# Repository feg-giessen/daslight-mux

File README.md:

# Daslight MUX #

Encoder to connect multiple buttons to the "port" connection of Daslight DMX interfaces: [http://www.daslight.com/online_manuals/en/750-823-FT8p45-Fj5plXXh3dfPJk8.htm](http://www.daslight.com/online_manuals/en/750-823-FT8p45-Fj5plXXh3dfPJk8.htm)

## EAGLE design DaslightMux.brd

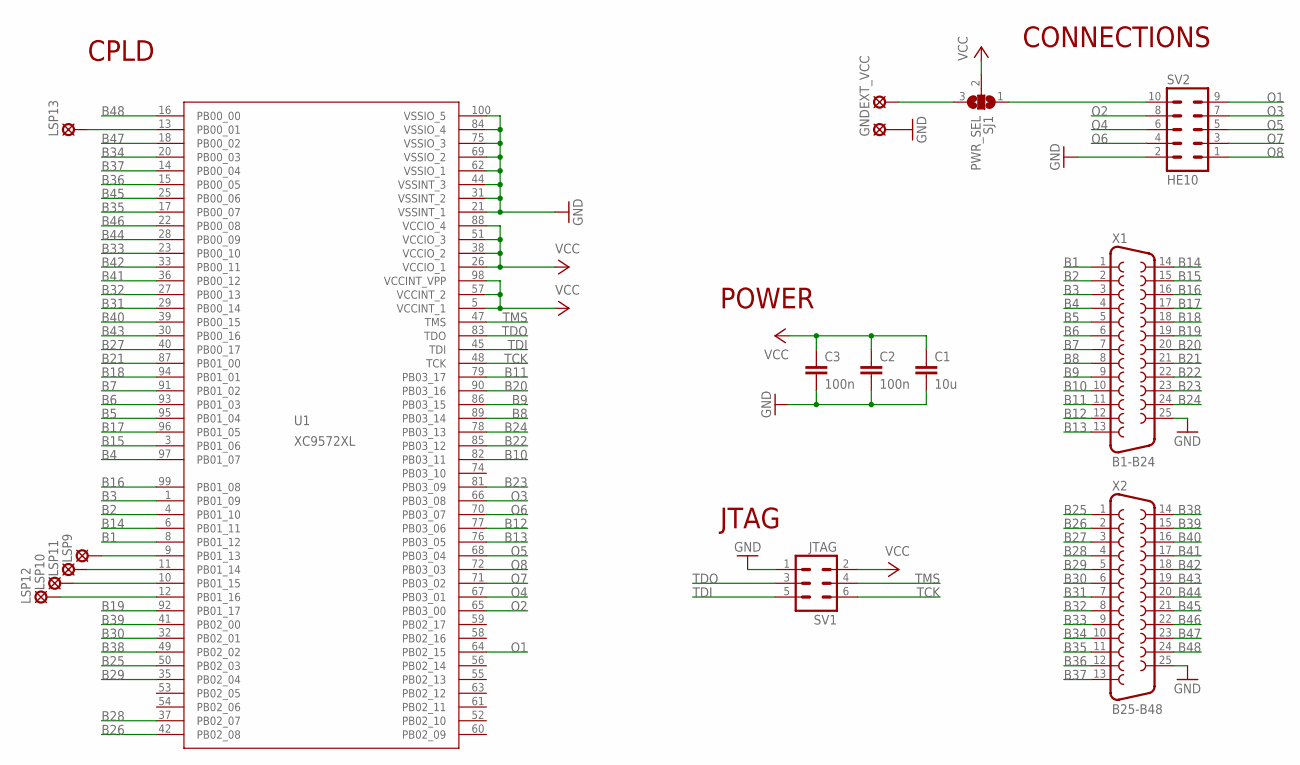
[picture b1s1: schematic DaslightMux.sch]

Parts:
C1: 10u; C1206
C2, C3: 100n; C0603
EXT_VCC: LSP10
GND: LSP10
LSP9, LSP10, LSP11, LSP12, LSP13: LSP10
SJ1: PWR_SEL; SJ_2
SV1: JTAG; MA03-2
SV2: HE10; ML10L
U1: XC9572XL; TQ100
X1: B1-B24; F25HP
X2: B25-B48; F25HP

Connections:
B1: U1.8 (PB01_12), X1.1
B2: U1.4 (PB01_10), X1.2
B3: U1.1 (PB01_09), X1.3
B4: U1.97 (PB01_07), X1.4
B5: U1.95 (PB01_04), X1.5
B6: U1.93 (PB01_03), X1.6
B7: U1.91 (PB01_02), X1.7
B8: U1.89 (PB03_14), X1.8
B9: U1.86 (PB03_15), X1.9
B10: U1.82 (PB03_11), X1.10
B11: U1.79 (PB03_17), X1.11
B12: U1.77 (PB03_06), X1.12
B13: U1.76 (PB03_05), X1.13
B14: U1.6 (PB01_11), X1.14
B15: U1.3 (PB01_06), X1.15
B16: U1.99 (PB01_08), X1.16
B17: U1.96 (PB01_05), X1.17
B18: U1.94 (PB01_01), X1.18
B19: U1.92 (PB01_17), X1.19
B20: U1.90 (PB03_16), X1.20
B21: U1.87 (PB01_00), X1.21
B22: U1.85 (PB03_12), X1.22
B23: U1.81 (PB03_09), X1.23
B24: U1.78 (PB03_13), X1.24
B25: U1.50 (PB02_03), X2.1
B26: U1.42 (PB02_08), X2.2
B27: U1.40 (PB00_17), X2.3
B28: U1.37 (PB02_07), X2.4
B29: U1.35 (PB02_04), X2.5
B30: U1.32 (PB02_01), X2.6
B31: U1.29 (PB00_14), X2.7
B32: U1.27 (PB00_13), X2.8
B33: U1.23 (PB00_10), X2.9
B34: U1.20 (PB00_03), X2.10
B35: U1.17 (PB00_07), X2.11
B36: U1.15 (PB00_05), X2.12
B37: U1.14 (PB00_04), X2.13
B38: U1.49 (PB02_02), X2.14
B39: U1.41 (PB02_00), X2.15
B40: U1.39 (PB00_15), X2.16
B41: U1.36 (PB00_12), X2.17
B42: U1.33 (PB00_11), X2.18
B43: U1.30 (PB00_16), X2.19
B44: U1.28 (PB00_09), X2.20
B45: U1.25 (PB00_06), X2.21
B46: U1.22 (PB00_08), X2.22
B47: U1.18 (PB00_02), X2.23
B48: U1.16 (PB00_00), X2.24
GND: C1.2, C2.2, C3.2, GND.MP, SV1.1, SV2.2, U1.21 (VSSINT_1), U1.31 (VSSINT_2), U1.44 (VSSINT_3), U1.62 (VSSIO_1), U1.69 (VSSIO_2), U1.75 (VSSIO_3), U1.84 (VSSIO_4), U1.100 (VSSIO_5), X1.25, X2.25
unnamed: SJ1.1, SV2.10
unnamed: EXT_VCC.MP, SJ1.3
unnamed: LSP9.MP, U1.9 (PB01_13)
unnamed: LSP10.MP, U1.10 (PB01_15)
unnamed: LSP11.MP, U1.11 (PB01_14)
unnamed: LSP12.MP, U1.12 (PB01_16)
unnamed: LSP13.MP, U1.13 (PB00_01)
O1: SV2.9, U1.64 (PB02_15)
O2: SV2.8, U1.65 (PB03_00)
O3: SV2.7, U1.66 (PB03_08)
O4: SV2.6, U1.67 (PB03_01)
O5: SV2.5, U1.68 (PB03_04)
O6: SV2.4, U1.70 (PB03_07)
O7: SV2.3, U1.71 (PB03_02)
O8: SV2.1, U1.72 (PB03_03)
TCK: SV1.6, U1.48 (TCK)
TDI: SV1.5, U1.45 (TDI)
TDO: SV1.3, U1.83 (TDO)
TMS: SV1.4, U1.47 (TMS)
VCC: C1.1, C2.1, C3.1, SJ1.2, SV1.2, U1.5 (VCCINT_1), U1.26 (VCCIO_1), U1.38 (VCCIO_2), U1.51 (VCCIO_3), U1.57 (VCCINT_2), U1.88 (VCCIO_4), U1.98 (VCCINT_VPP)

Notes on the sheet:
POWER
JTAG
CONNECTIONS
CPLD

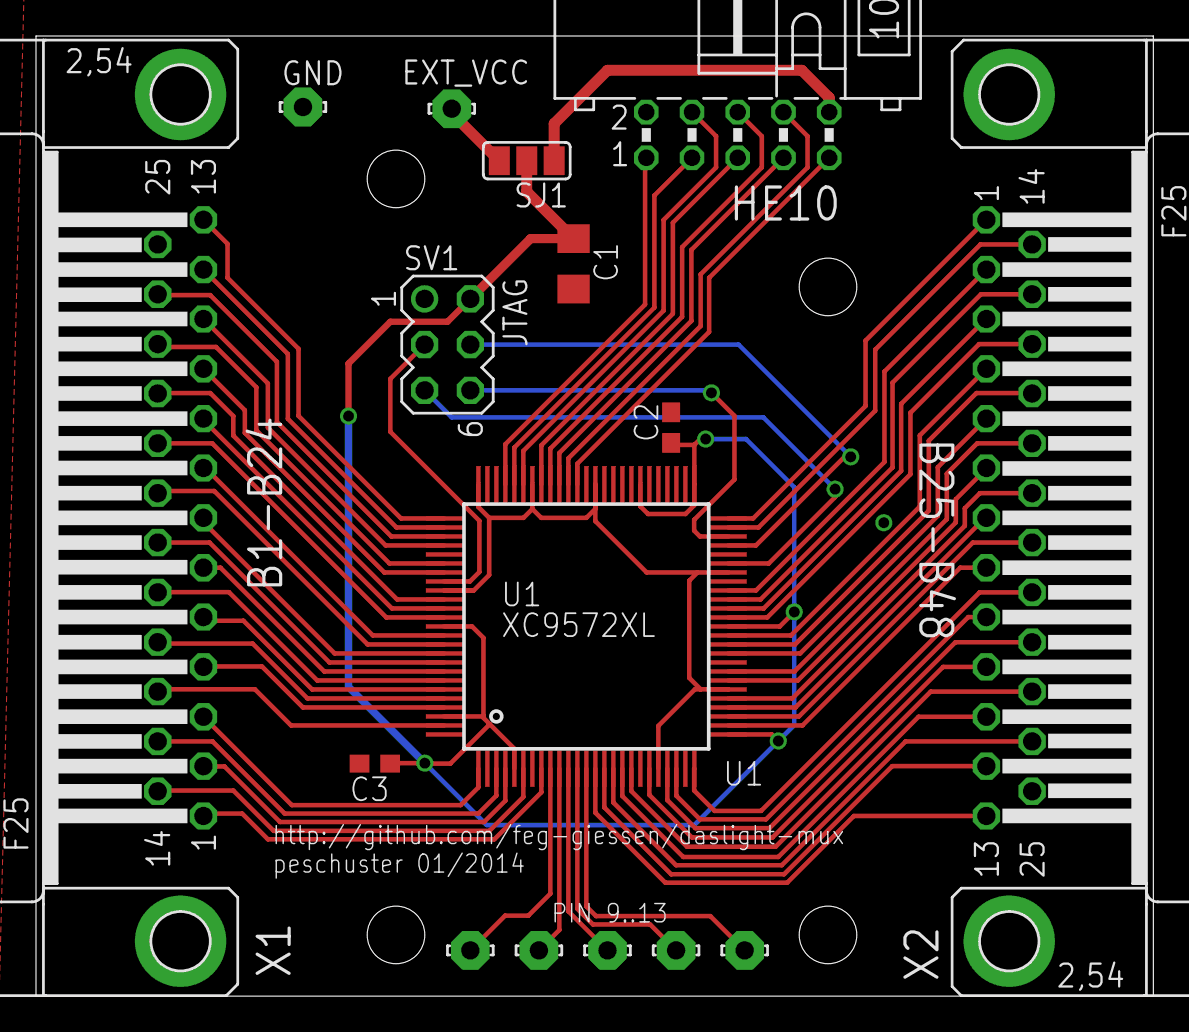
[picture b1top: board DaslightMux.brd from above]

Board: 2 copper layers, 62.1 x 53.3 mm, 16 parts (0 on the bottom side), 69 nets.

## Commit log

2014-01-07 Initial import.
2014-01-07 Added readme.
2014-01-07 Compiled xsvf
2014-01-07 Cleanup, enclosure.
2014-01-08 VHDL cleanup and simulation
2014-01-08 Schematic & enclosure
2014-01-08 Seperated rtl and cpld implementation.
2014-01-09 Changed to SUB-D, therefore swapped "all" pins
2014-01-09 Remodeled enclosure and adapted pcb layout
2014-01-09 Added 'U1' label outside ic area.
2014-01-11 Ordered version of pcb
    (added solder pads for pins 9-13)
2014-01-16 3D view
